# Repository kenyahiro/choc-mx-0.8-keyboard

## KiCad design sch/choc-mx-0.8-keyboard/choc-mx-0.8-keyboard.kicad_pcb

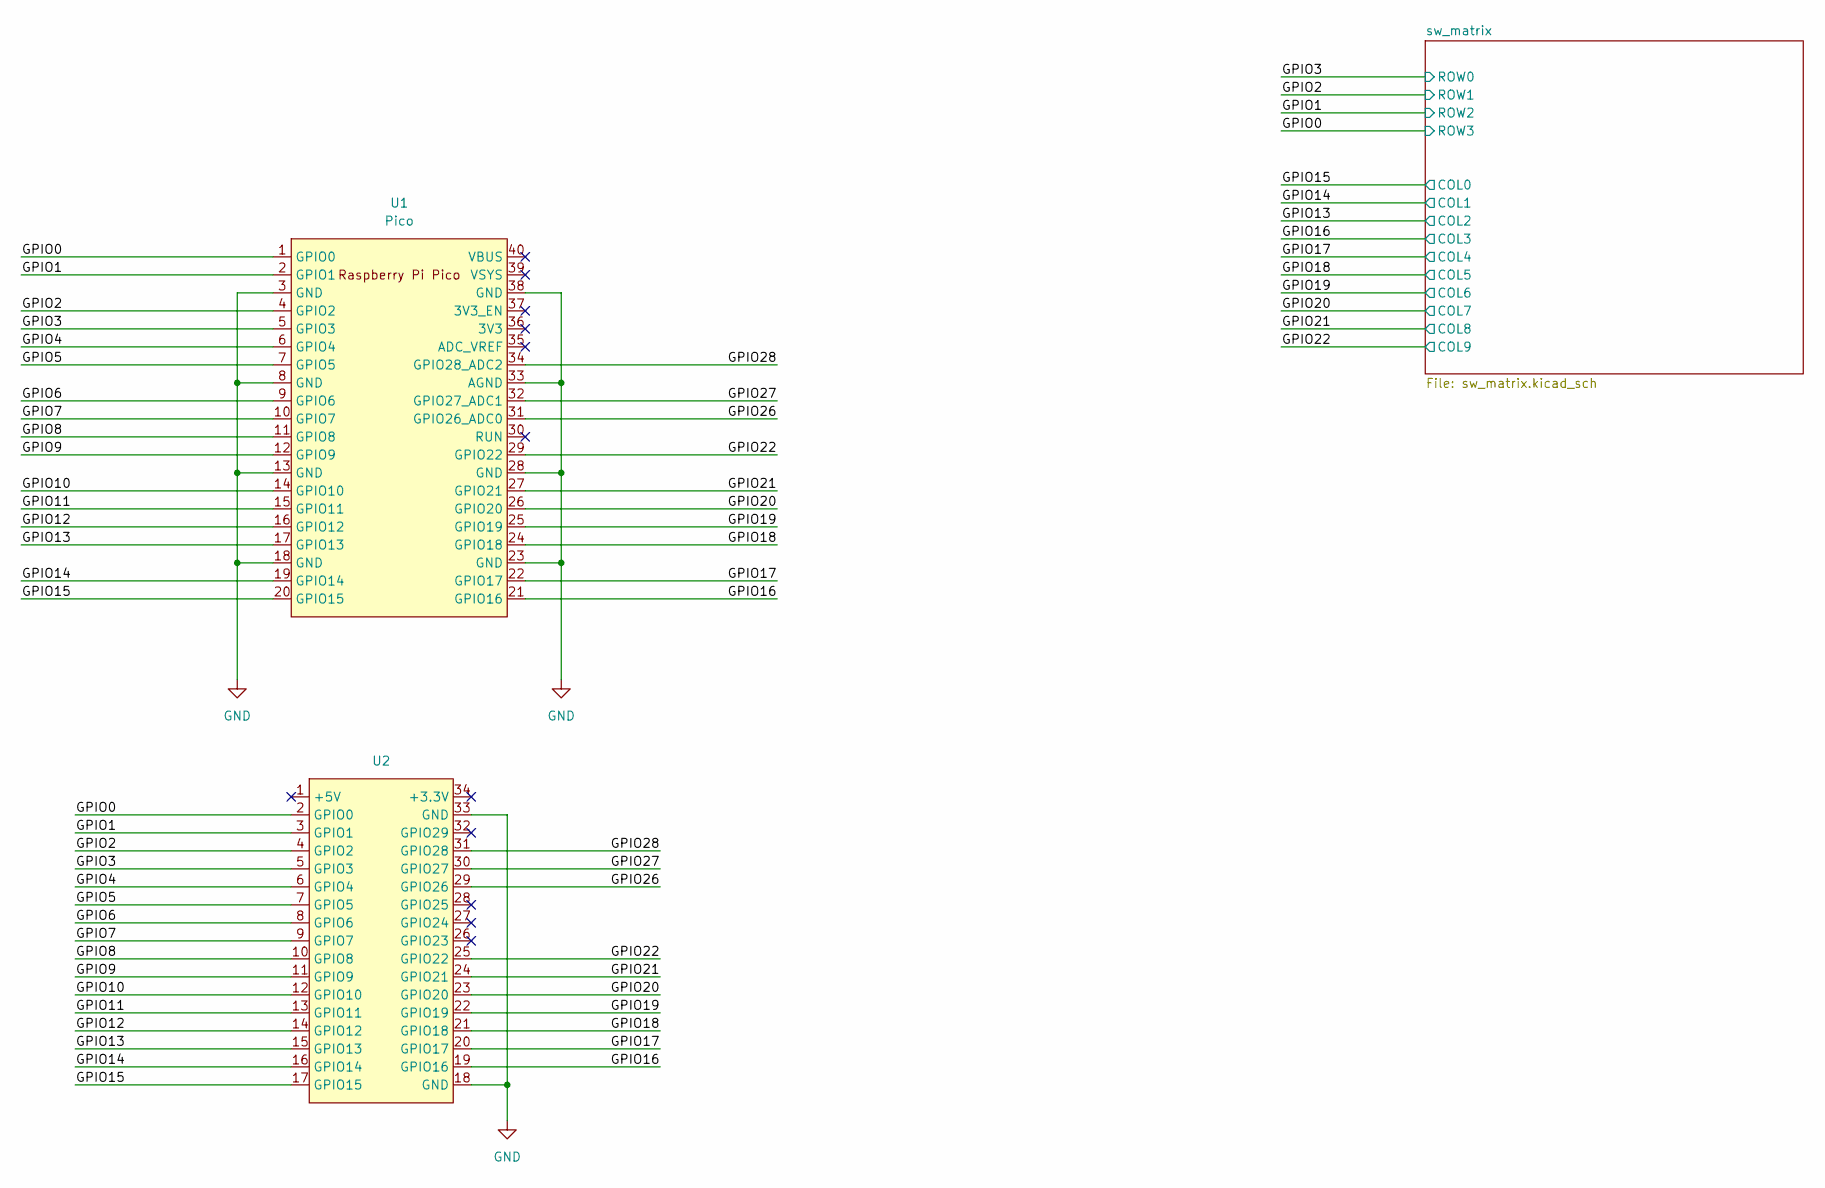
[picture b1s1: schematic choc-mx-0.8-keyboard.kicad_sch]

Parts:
U1: Pico; pico_no_dbg_th
U2: AE-RP2040

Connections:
/GPIO0: U1.1 (GPIO0), U2.2 (GPIO0); also elsewhere on the board
/GPIO1: U1.2 (GPIO1), U2.3 (GPIO1); also elsewhere on the board
/GPIO2: U1.4 (GPIO2), U2.4 (GPIO2); also elsewhere on the board
/GPIO3: U1.5 (GPIO3), U2.5 (GPIO3); also elsewhere on the board
/GPIO4: U1.6 (GPIO4), U2.6 (GPIO4)
/GPIO5: U1.7 (GPIO5), U2.7 (GPIO5)
/GPIO6: U1.9 (GPIO6), U2.8 (GPIO6)
/GPIO7: U1.10 (GPIO7), U2.9 (GPIO7)
/GPIO8: U1.11 (GPIO8), U2.10 (GPIO8)
/GPIO9: U1.12 (GPIO9), U2.11 (GPIO9)
/GPIO10: U1.14 (GPIO10), U2.12 (GPIO10)
/GPIO11: U1.15 (GPIO11), U2.13 (GPIO11)
/GPIO12: U1.16 (GPIO12), U2.14 (GPIO12)
/GPIO13: U1.17 (GPIO13), U2.15 (GPIO13); also elsewhere on the board
/GPIO14: U1.19 (GPIO14), U2.16 (GPIO14); also elsewhere on the board
/GPIO15: U1.20 (GPIO15), U2.17 (GPIO15); also elsewhere on the board
/GPIO16: U1.21 (GPIO16), U2.19 (GPIO16); also elsewhere on the board
/GPIO17: U1.22 (GPIO17), U2.20 (GPIO17); also elsewhere on the board
/GPIO18: U1.24 (GPIO18), U2.21 (GPIO18); also elsewhere on the board
/GPIO19: U1.25 (GPIO19), U2.22 (GPIO19); also elsewhere on the board
/GPIO20: U1.26 (GPIO20), U2.23 (GPIO20); also elsewhere on the board
/GPIO21: U1.27 (GPIO21), U2.24 (GPIO21); also elsewhere on the board
/GPIO22: U1.29 (GPIO22), U2.25 (GPIO22); also elsewhere on the board
/GPIO26: U1.31 (GPIO26_ADC0), U2.29 (GPIO26)
/GPIO27: U1.32 (GPIO27_ADC1), U2.30 (GPIO27)
/GPIO28: U1.34 (GPIO28_ADC2), U2.31 (GPIO28)
GND: U1.3 (GND), U1.8 (GND), U1.13 (GND), U1.18 (GND), U1.23 (GND), U1.28 (GND), U1.33 (AGND), U1.38 (GND), U2.18 (GND), U2.33 (GND)

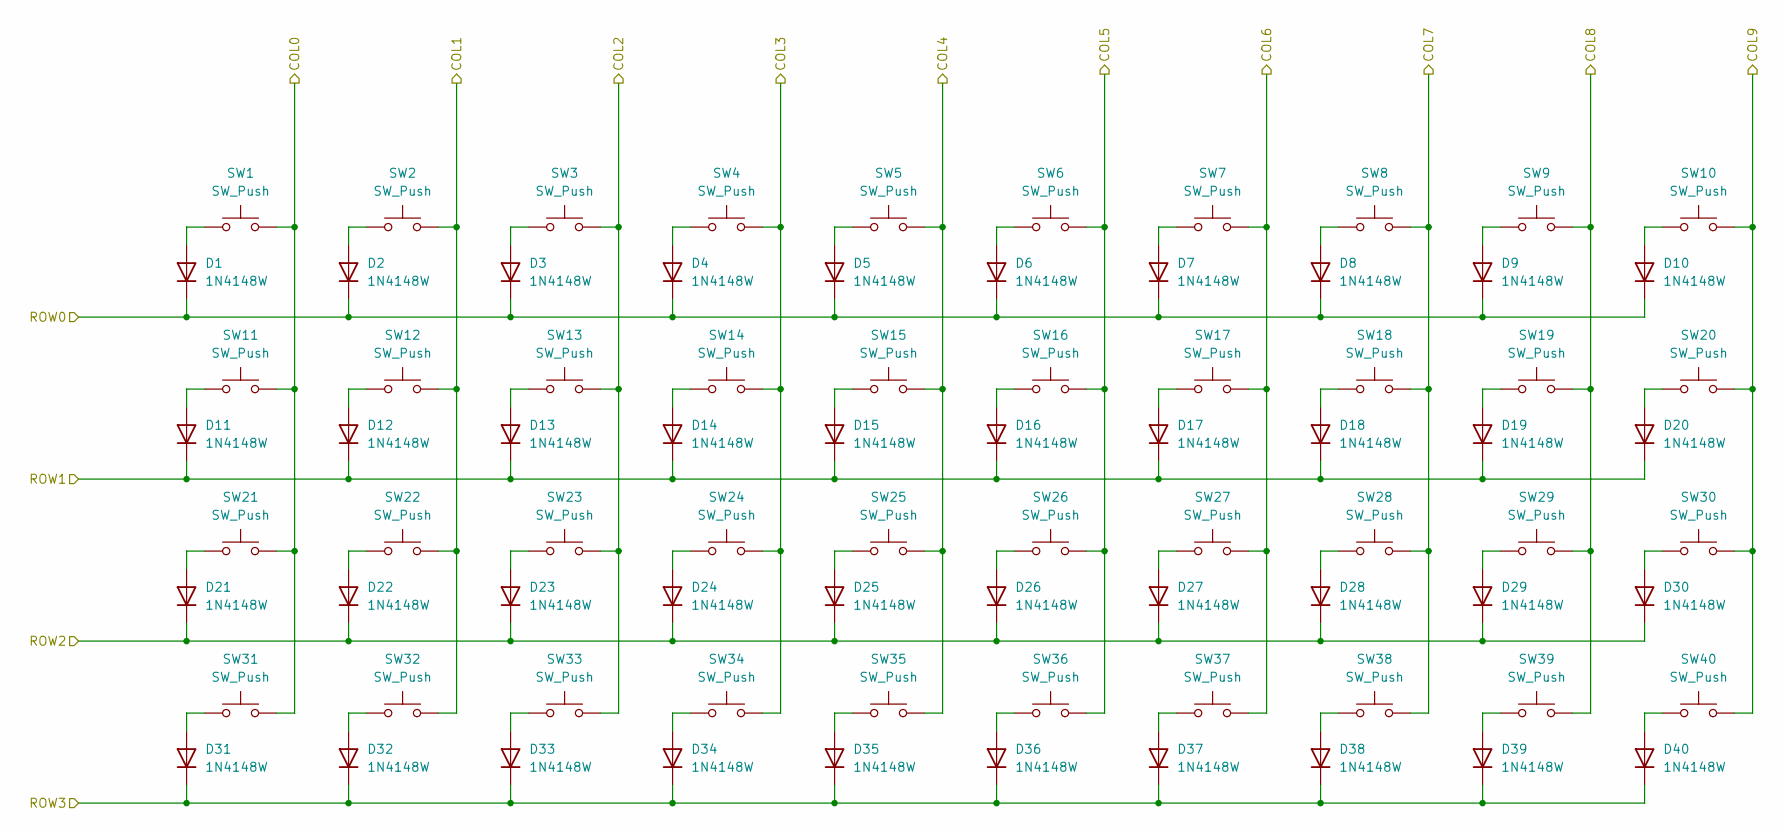
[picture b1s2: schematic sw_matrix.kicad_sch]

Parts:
D1, D2, D3, D4, D5, D6, D7, D8, D9, D10, D11, D12, D13, D14, D15, D16, D17, D18, D19, D20, D21, D22, D23, D24, D25, D26, D27, D28, D29, D30, D31, D32, D33, D34, D35, D36, D37, D38, D39, D40: 1N4148W; D_SOD-123
SW1, SW2, SW3, SW4, SW5, SW6, SW7, SW8, SW9, SW10, SW11, SW12, SW13, SW14, SW15, SW16, SW17, SW18, SW19, SW20, SW21, SW22, SW23, SW24, SW25, SW26, SW27, SW28, SW29, SW30, SW31, SW32, SW33, SW34, SW35, SW36, SW37, SW38, SW39, SW40: SW_Push; CherryMX_MidHeight_Choc_Hotswap_rev1_mod

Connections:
/GPIO0: D31.1 (K), D32.1 (K), D33.1 (K), D34.1 (K), D35.1 (K), D36.1 (K), D37.1 (K), D38.1 (K), D39.1 (K), D40.1 (K); also elsewhere on the board
/GPIO1: D21.1 (K), D22.1 (K), D23.1 (K), D24.1 (K), D25.1 (K), D26.1 (K), D27.1 (K), D28.1 (K), D29.1 (K), D30.1 (K); also elsewhere on the board
/GPIO2: D11.1 (K), D12.1 (K), D13.1 (K), D14.1 (K), D15.1 (K), D16.1 (K), D17.1 (K), D18.1 (K), D19.1 (K), D20.1 (K); also elsewhere on the board
/GPIO3: D1.1 (K), D2.1 (K), D3.1 (K), D4.1 (K), D5.1 (K), D6.1 (K), D7.1 (K), D8.1 (K), D9.1 (K), D10.1 (K); also elsewhere on the board
/GPIO13: SW3.2, SW13.2, SW23.2, SW33.2; also elsewhere on the board
/GPIO14: SW2.2, SW12.2, SW22.2, SW32.2; also elsewhere on the board
/GPIO15: SW1.2, SW11.2, SW21.2, SW31.2; also elsewhere on the board
/GPIO16: SW4.2, SW14.2, SW24.2, SW34.2; also elsewhere on the board
/GPIO17: SW5.2, SW15.2, SW25.2, SW35.2; also elsewhere on the board
/GPIO18: SW6.2, SW16.2, SW26.2, SW36.2; also elsewhere on the board
/GPIO19: SW7.2, SW17.2, SW27.2, SW37.2; also elsewhere on the board
/GPIO20: SW8.2, SW18.2, SW28.2, SW38.2; also elsewhere on the board
/GPIO21: SW9.2, SW19.2, SW29.2, SW39.2; also elsewhere on the board
/GPIO22: SW10.2, SW20.2, SW30.2, SW40.2; also elsewhere on the board
unnamed: D1.2 (A), SW1.1
unnamed: D2.2 (A), SW2.1
unnamed: D3.2 (A), SW3.1
unnamed: D4.2 (A), SW4.1
unnamed: D5.2 (A), SW5.1
unnamed: D6.2 (A), SW6.1
unnamed: D7.2 (A), SW7.1
unnamed: D8.2 (A), SW8.1
unnamed: D9.2 (A), SW9.1
unnamed: D10.2 (A), SW10.1
unnamed: D11.2 (A), SW11.1
unnamed: D12.2 (A), SW12.1
unnamed: D13.2 (A), SW13.1
unnamed: D14.2 (A), SW14.1
unnamed: D15.2 (A), SW15.1
unnamed: D16.2 (A), SW16.1
unnamed: D17.2 (A), SW17.1
unnamed: D18.2 (A), SW18.1
unnamed: D19.2 (A), SW19.1
unnamed: D20.2 (A), SW20.1
unnamed: D21.2 (A), SW21.1
unnamed: D22.2 (A), SW22.1
unnamed: D23.2 (A), SW23.1
unnamed: D24.2 (A), SW24.1
unnamed: D25.2 (A), SW25.1
unnamed: D26.2 (A), SW26.1
unnamed: D27.2 (A), SW27.1
unnamed: D28.2 (A), SW28.1
unnamed: D29.2 (A), SW29.1
unnamed: D30.2 (A), SW30.1
unnamed: D31.2 (A), SW31.1
unnamed: D32.2 (A), SW32.1
unnamed: D33.2 (A), SW33.1
unnamed: D34.2 (A), SW34.1
unnamed: D35.2 (A), SW35.1
unnamed: D36.2 (A), SW36.1
unnamed: D37.2 (A), SW37.1
unnamed: D38.2 (A), SW38.1
unnamed: D39.2 (A), SW39.1
unnamed: D40.2 (A), SW40.1

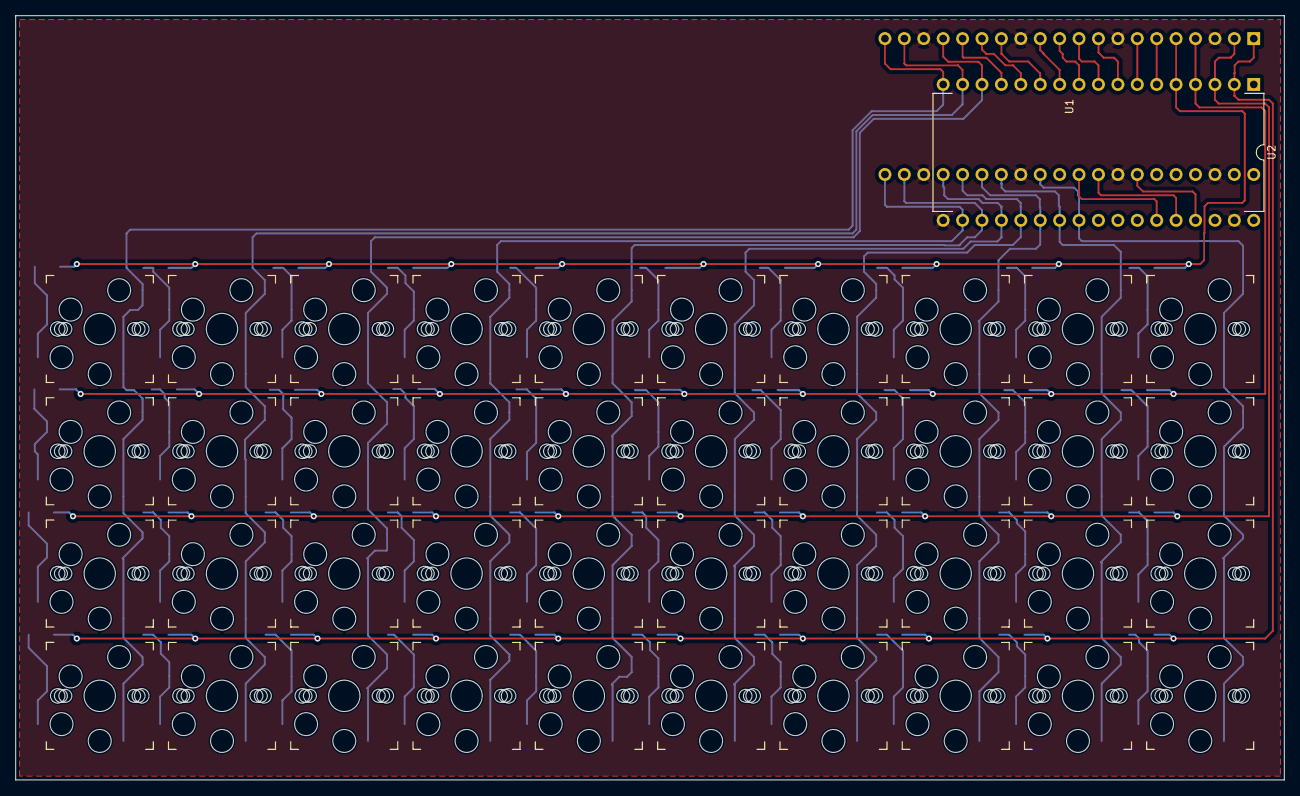
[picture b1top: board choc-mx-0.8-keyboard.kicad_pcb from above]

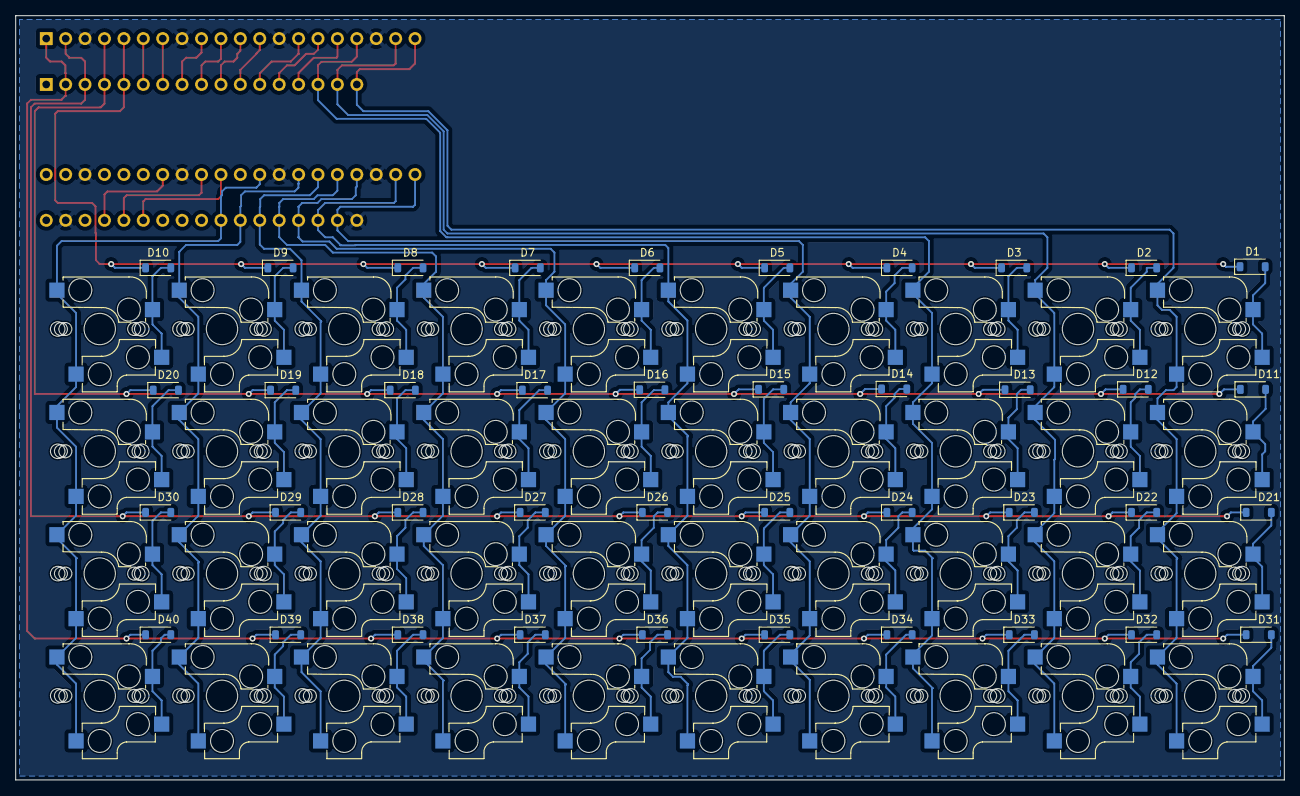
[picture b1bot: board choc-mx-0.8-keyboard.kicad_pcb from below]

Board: 2 copper layers, 166.0 x 100.0 mm, 82 parts (40 on the bottom side), 67 nets.

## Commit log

2023-08-27 挟ピッチの40%キーボードです。 Raspberry Pi pico を使って配線しました。
2023-08-27 回路図のPDFを追加。
2023-08-27 AE-RP2040も使えるようにしました。
